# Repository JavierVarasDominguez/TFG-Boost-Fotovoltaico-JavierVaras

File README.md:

# Diseño y estudio de un convertidor DC-DC Boost para carga de vehículos eléctricos a partir de energía fotovoltaica

Repositorio asociado al Trabajo Fin de Grado:

**Diseño y estudio de un convertidor DC-DC Boost para carga de vehículos eléctricos a partir de energía fotovoltaica**
**Autor:** Javier Varas Domínguez
**Titulación:** Grado en Ingeniería Electrónica Industrial y Automática
**Universidad:** Universidad de Cantabria
**Tutor:** Francisco Javier Díaz Rodríguez
**Curso:** 2025/2026

---

## Descripción del proyecto

Este proyecto tiene como objetivo el diseño, simulación y validación de un convertidor DC-DC tipo Boost aplicado a un sistema de carga de baterías de vehículos eléctricos alimentado mediante energía fotovoltaica.

El sistema parte de una instalación fotovoltaica residencial de aproximadamente 2,4 kW, formada por seis módulos conectados en serie. La tensión generada por el campo fotovoltaico se eleva mediante un convertidor Boost hasta un nivel adecuado para la carga de baterías de vehículos eléctricos.

Además del diseño teórico del convertidor, se ha desarrollado un modelo de simulación en MATLAB/Simulink, se ha implementado un algoritmo MPPT basado en el método de perturbación y observación, y se ha construido un prototipo experimental a escala reducida controlado mediante ESP32S.

---

## Objetivos principales

* Diseñar un convertidor DC-DC tipo Boost para una aplicación fotovoltaica orientada a la carga de vehículos eléctricos.
* Dimensionar los principales componentes de la etapa de potencia.
* Simular el comportamiento del sistema en MATLAB/Simulink.
* Implementar un algoritmo MPPT para mejorar el aprovechamiento de la energía disponible.
* Diseñar y fabricar una PCB para el prototipo experimental.
* Validar el funcionamiento del sistema mediante un prototipo a escala reducida.

---

## Estructura del repositorio

```text
TFG-Boost-Fotovoltaico-JavierVaras/
│
├── Simulink_Matlab/
│   ├── 04_Simulaciones_Convertidor/
│   └── Prototipo/
│
├── Codigos_Control_ESP32/
│
├── KiCad_Prototipo/
│
├── Documentacion_TFG/

```

### Simulink_Matlab

Contiene los modelos de simulación desarrollados en MATLAB/Simulink.
Incluye las simulaciones del convertidor Boost, el funcionamiento con ciclo de trabajo fijo, la implementación del algoritmo MPPT y la validación del prototipo experimental.

### Codigos_Control_ESP32

Incluye los códigos utilizados para el control del prototipo mediante ESP32S.
Se recogen tanto las pruebas de generación PWM como la implementación del algoritmo MPPT.

### KiCad_Prototipo

Contiene los archivos relacionados con el diseño electrónico del prototipo.
Incluye el esquemático, el diseño de la PCB y los archivos necesarios para documentar la placa desarrollada.

### Documentacion_TFG

Carpeta destinada a recoger la memoria del Trabajo Fin de Grado y documentación complementaria.

### Resultados_Experimentales

Incluye capturas, medidas de laboratorio y fotografías relacionadas con las pruebas del prototipo experimental.

---

## Herramientas utilizadas

* MATLAB/Simulink
* KiCad
* Arduino IDE
* ESP32S
* Osciloscopio y fuente de alimentación de laboratorio
* Instrumentación básica de medida

---

## Contenido técnico del proyecto

El trabajo incluye:

* Estudio del funcionamiento del convertidor Boost en modo de conducción continua.
* Cálculo del ciclo de trabajo para distintos valores de tensión de entrada.
* Dimensionado de la inductancia y condensadores.
* Selección de MOSFET, diodo, driver de puerta y componentes auxiliares.
* Simulación del convertidor en lazo abierto.
* Implementación del algoritmo MPPT mediante perturbación y observación.
* Análisis ante variaciones de irradiancia.
* Diseño de un prototipo experimental a escala reducida.
* Diseño y fabricación de la PCB.
* Validación experimental mediante medidas de laboratorio.

---

## Prototipo experimental

El prototipo se ha desarrollado a escala reducida para validar el funcionamiento básico del convertidor y del sistema de control.
La etapa de potencia se ha diseñado como un convertidor Boost alimentado a baja tensión, controlado mediante una señal PWM generada por un ESP32S.

El objetivo del prototipo no es replicar la potencia del sistema fotovoltaico completo, sino comprobar de forma práctica el comportamiento del convertidor, la generación de la señal de control y la respuesta del algoritmo MPPT.

---

## Nota

Este repositorio se ha creado como complemento a la memoria del Trabajo Fin de Grado.
Los archivos incluidos tienen finalidad académica y sirven para documentar el desarrollo del proyecto, las simulaciones realizadas, el diseño de la PCB y las pruebas experimentales llevadas a cabo.

---

## Autor

**Javier Varas Domínguez**
Grado en Ingeniería Electrónica Industrial y Automática
Universidad de Cantabria

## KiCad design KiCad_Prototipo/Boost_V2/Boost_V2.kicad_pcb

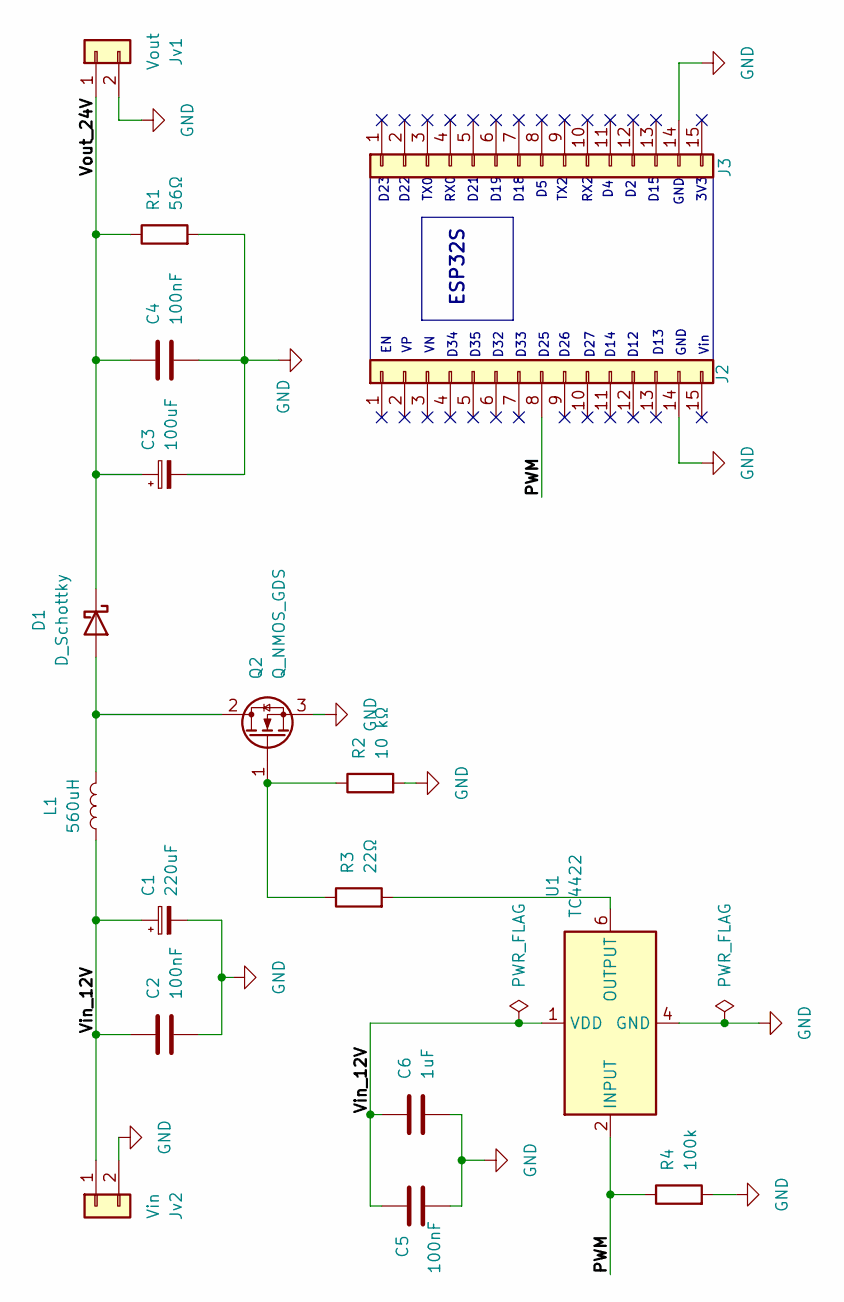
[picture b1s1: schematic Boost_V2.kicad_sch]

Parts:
C1: 220uF; CP_Radial_D8.0mm_P3.50mm
C2, C4, C5: 100nF; C_Disc_D5.0mm_W2.5mm_P5.00mm
C3: 100uF; CP_Radial_D8.0mm_P3.50mm
C6: 1uF; CP_Radial_D8.0mm_P3.50mm
D1: D_Schottky; D_DO-41_SOD81_P10.16mm_Horizontal
J2, J3: Conn_01x15; PinSocket_1x15_P2.54mm_Vertical
Jv1: Vout; TerminalBlock_Phoenix_MKDS-1,5-2-5.08_1x02_P5.08mm_Horizont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
Jv2: Vin; TerminalBlock_Phoenix_MKDS-1,5-2-5.08_1x02_P5.08mm_Horizont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
L1: 560uH; L_Radial_D10.0mm_P5.00mm_Fastron_07M
Q2: Q_NMOS_GDS; TO-220-3_Vertical
R1: 56Ω; R_Axial_Power_L20.0mm_W6.4mm_P25.40mm
R2: 10 kΩ; R_Axial_DIN0207_L6.3mm_D2.5mm_P7.62mm_Horizontal
R3: 22Ω; R_Axial_DIN0207_L6.3mm_D2.5mm_P7.62mm_Horizontal
R4: 100k; R_Axial_DIN0207_L6.3mm_D2.5mm_P7.62mm_Horizontal
U1: TC4422; DIP-8_W7.62mm

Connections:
/PWM: J2.8, R4.1, U1.2 (INPUT)
/Vin_12V: C1.1, C2.1, C5.1, C6.1, Jv2.1, L1.1, U1.1 (VDD), U1.8 (VDD)
/Vout_24V: C3.1, C4.1, D1.1 (K), Jv1.1, R1.1
GND: C1.2, C2.2, C3.2, C4.2, C5.2, C6.2, J2.14, J3.14 (Pin_14_14), Jv1.2, Jv2.2, Q2.3 (S), R1.2, R2.2, R4.2, U1.4 (GND), U1.5 (GND)
unnamed: D1.2 (A), L1.2, Q2.2 (D)
unnamed: Q2.1 (G), R2.1, R3.1
unnamed: R3.2, U1.6 (OUTPUT), U1.7 (OUTPUT)

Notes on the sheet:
D34
TX0
D27
D26
3V3
D12
D14
D33
D21
GND
D32
RX0
D23
GND
D25
D18
Vin
D35
RX2
D15
D13
TX2
D19
D22
ESP32S

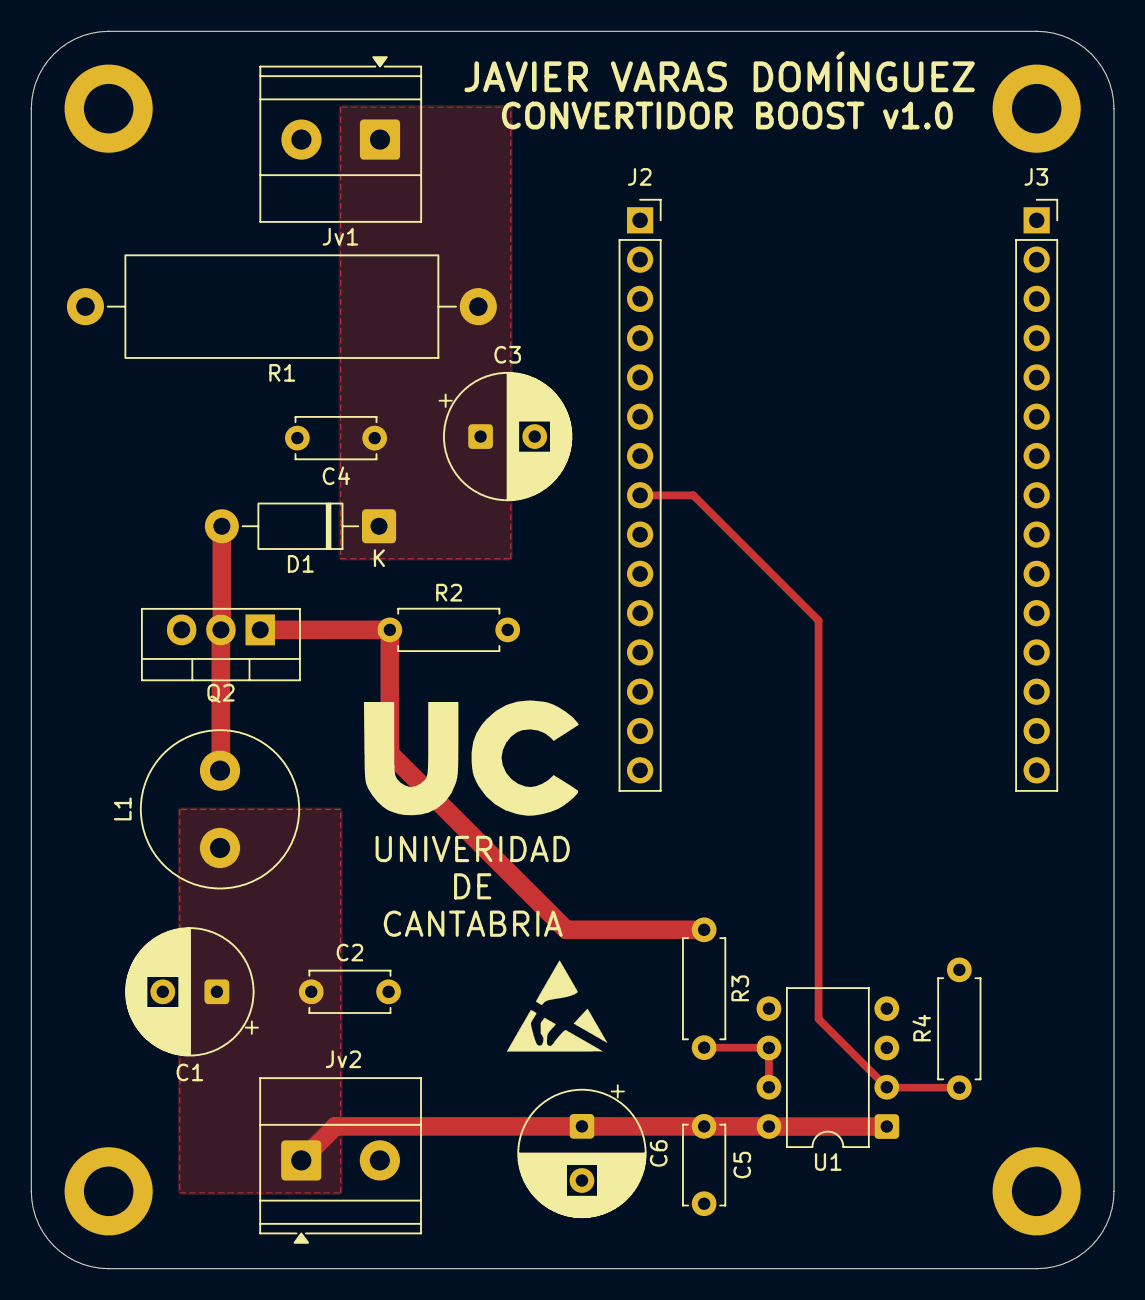
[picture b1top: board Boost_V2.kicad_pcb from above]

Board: 2 copper layers, 70.0 x 80.0 mm, 18 parts (0 on the bottom side), 7 nets.

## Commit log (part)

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2026-06-20 Simulink_Matlab
    En esta carpeta se recogen todos los archivos de MATLAB/Simulink utilizados tanto en la validación del sistema original como los archivos utilizados para el prototipo.
2026-06-22 Create Simulaciones Convertidor Boost
2026-06-22 Create MATLAB_Simulink
2026-06-22 Create .gitkeep
    Simulaciones utilizadas en el apartado 4 de la memoria
